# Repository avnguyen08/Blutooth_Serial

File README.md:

# Blutooth Serial

Board that steps down 24V to 3.3V and uses a HC-05 for UART to blutooth classic data conversion

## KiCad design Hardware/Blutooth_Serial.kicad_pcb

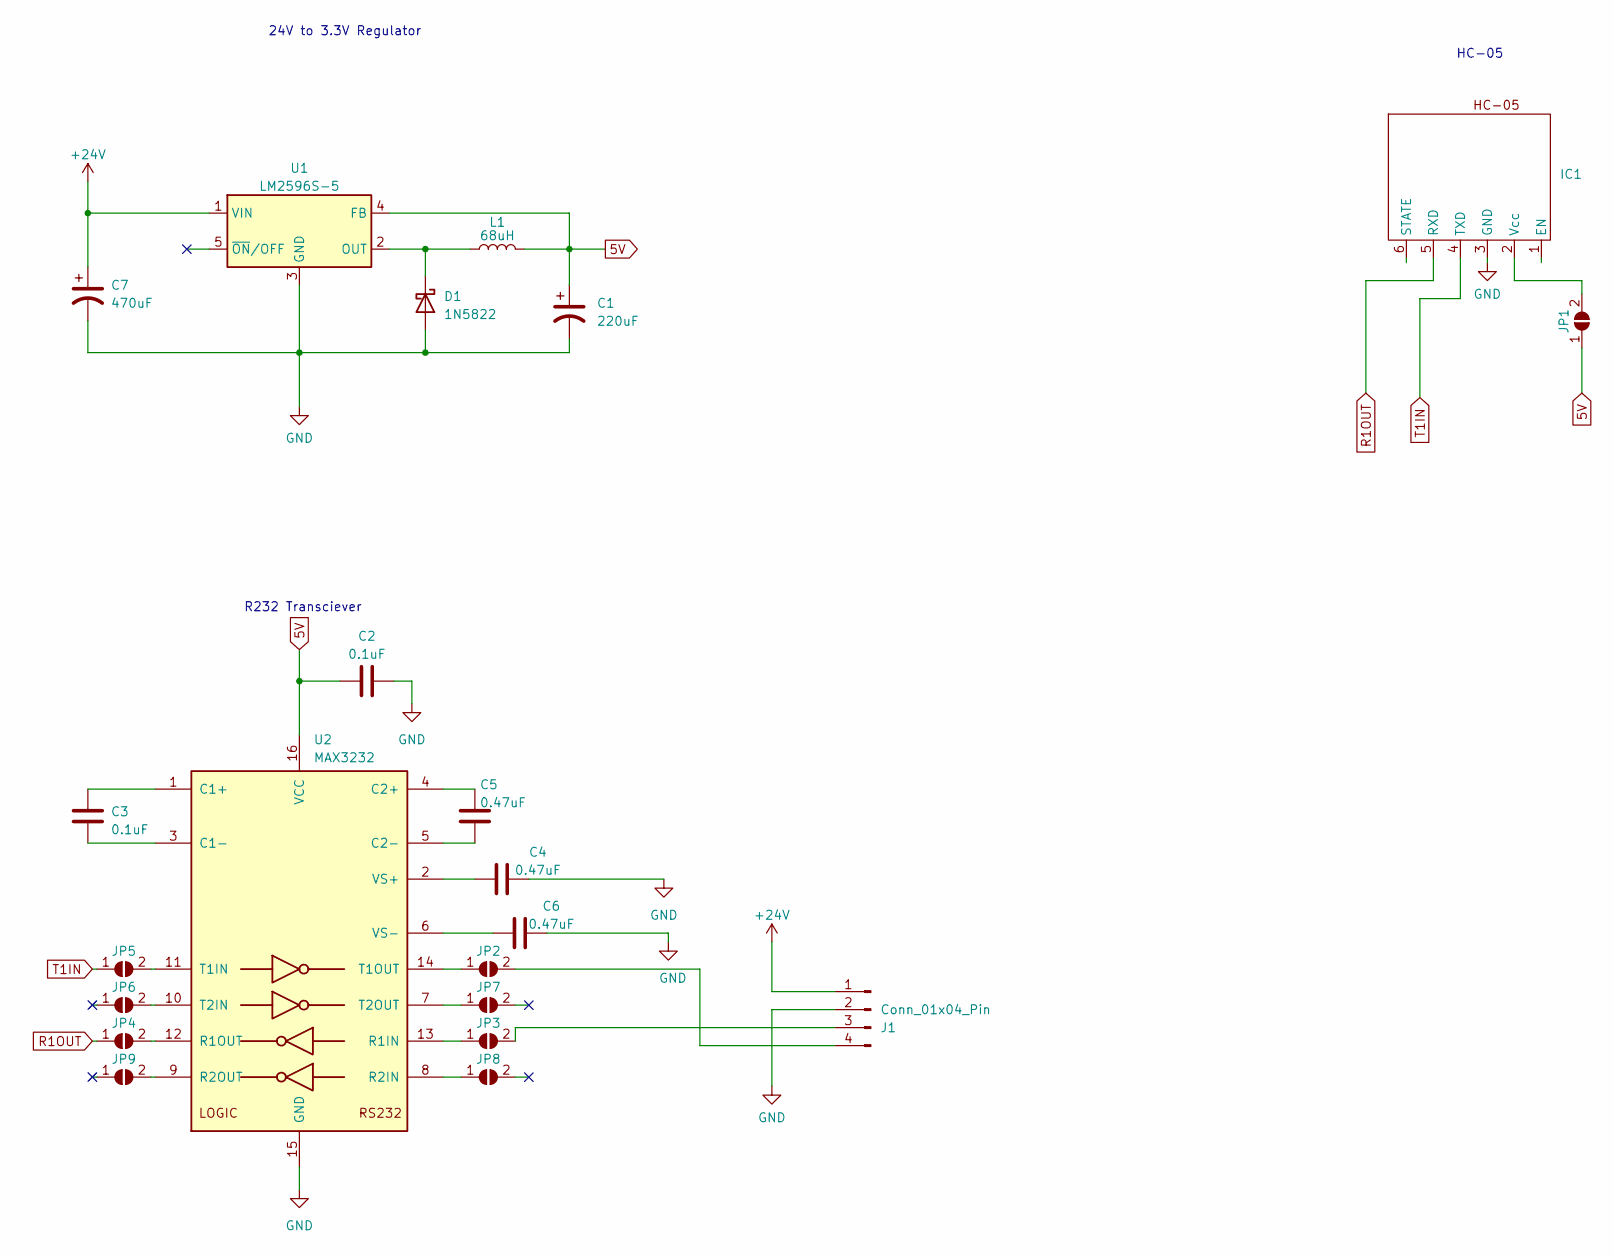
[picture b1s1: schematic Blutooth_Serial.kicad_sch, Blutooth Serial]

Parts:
C1: 220uF; 220uF_SMD_CAP
C2, C3: 0.1uF; C_0805_2012Metric
C4, C5, C6: 0.47uF; C_0805_2012Metric
C7: 470uF; 470uF_SMD_CAP
D1: 1N5822; D_0805_2012Metric
IC1: HC-05
J1: Conn_01x04_Pin; male_pin_4
JP1, JP2, JP3, JP4, JP5, JP6, JP7, JP8, JP9: SolderJumper_2_Open; SolderJumper-2_P1.3mm_Open_Pad1.0x1.5mm
L1: 68uH; L_12x12mm_H6mm
U1: LM2596S-5; TO-263-5_TabPin3
U2: MAX3232; MAX3232EIDR

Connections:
5V: C1.1, C2.1, JP1.1 (A), L1.2, U1.4 (FB), U2.16 (VCC)
+24V: C7.1, J1.1, U1.1 (VIN)
GND: C1.2, C2.2, C4.2, C6.2, C7.2, D1.2 (A), IC1.3 (GND), J1.2, U1.3 (GND), U2.15 (GND)
unnamed: D1.1 (K), L1.1, U1.2 (OUT)
unnamed: IC1.2 (Vcc), JP1.2 (B)
unnamed: J1.3, JP3.2 (B)
unnamed: J1.4, JP2.2 (B)
unnamed: JP2.1 (A), U2.14 (T1OUT)
unnamed: JP3.1 (A), U2.13 (R1IN)
unnamed: JP4.2 (B), U2.12 (R1OUT)
unnamed: JP5.2 (B), U2.11 (T1IN)
unnamed: JP6.2 (B), U2.10 (T2IN)
unnamed: JP7.1 (A), U2.7 (T2OUT)
unnamed: JP8.1 (A), U2.8 (R2IN)
unnamed: JP9.2 (B), U2.9 (R2OUT)
unnamed: C3.1, U2.1 (C1+)
unnamed: C3.2, U2.3 (C1-)
unnamed: C5.1, U2.4 (C2+)
unnamed: C5.2, U2.5 (C2-)
unnamed: C4.1, U2.2 (VS+)
unnamed: C6.1, U2.6 (VS-)
R1OUT: IC1.5 (RXD), JP4.1 (A)
T1IN: IC1.4 (TXD), JP5.1 (A)

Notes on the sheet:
R232 Transciever
24V to 3.3V Regulator
HC-05

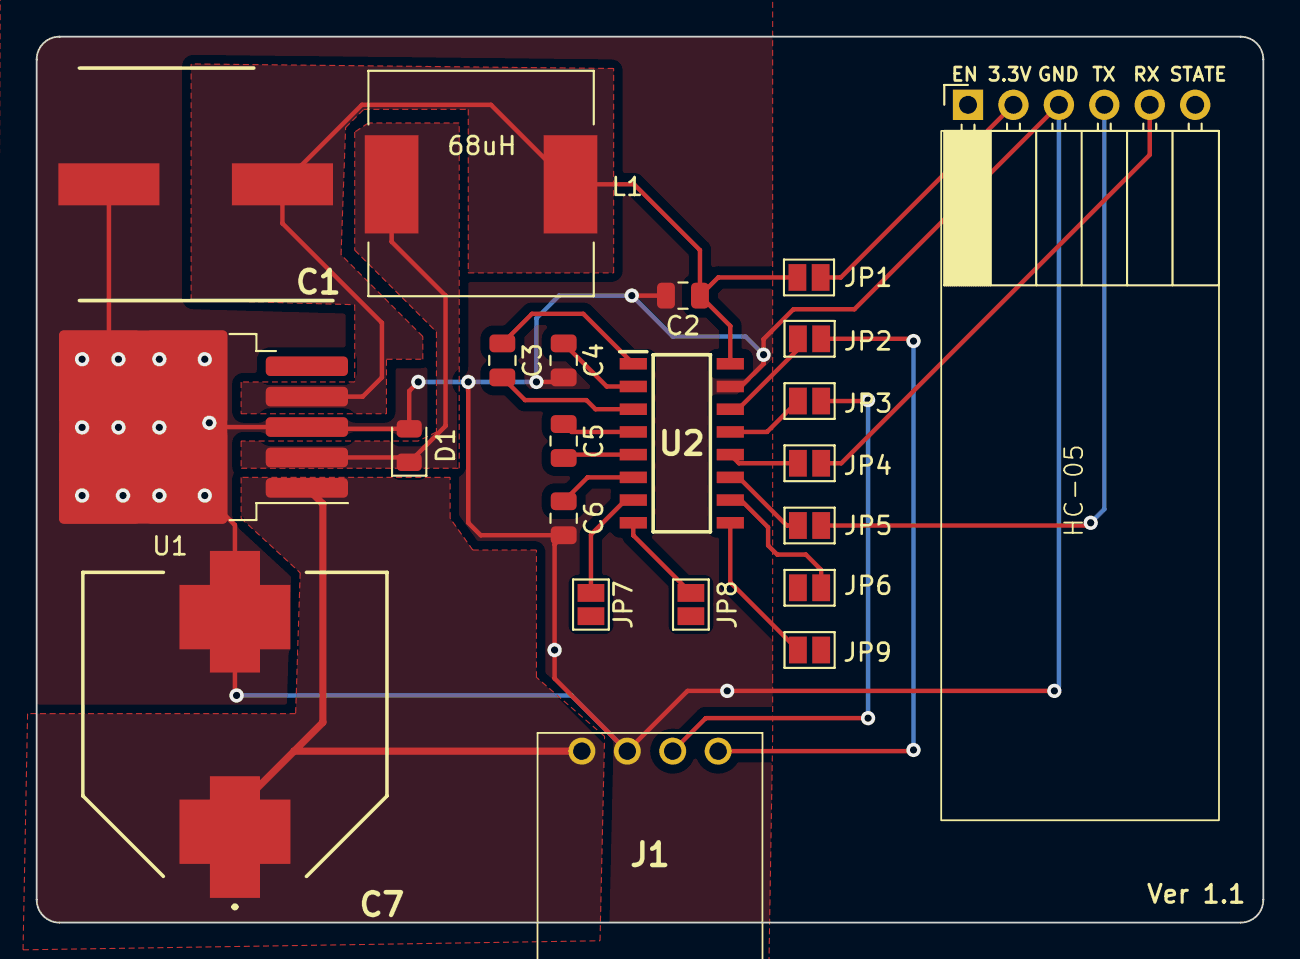
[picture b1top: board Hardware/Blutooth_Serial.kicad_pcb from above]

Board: 2 copper layers, 68.6 x 49.5 mm, 22 parts (0 on the bottom side), 23 nets.

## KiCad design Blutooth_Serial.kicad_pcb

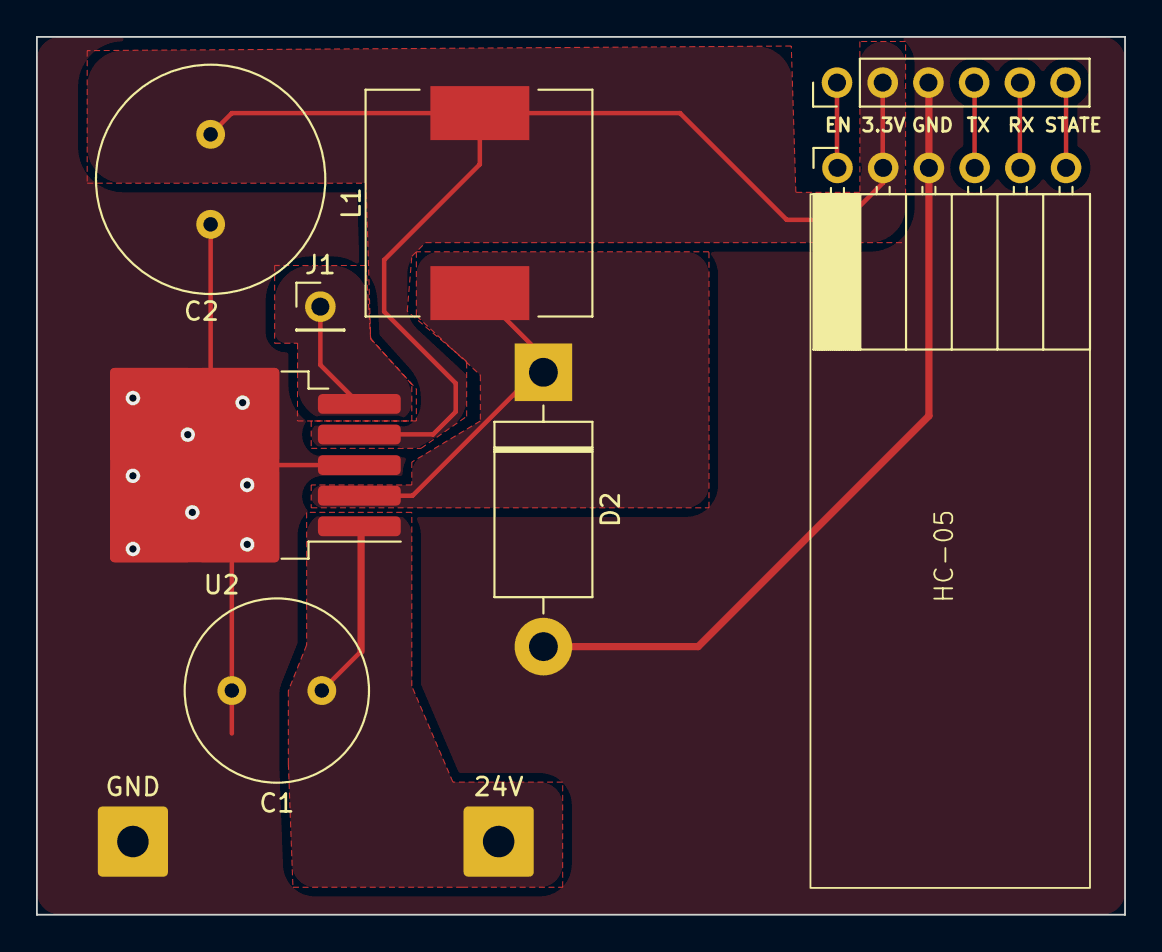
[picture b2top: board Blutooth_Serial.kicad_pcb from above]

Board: 2 copper layers, 60.5 x 48.8 mm, 9 parts (0 on the bottom side), 5 nets.

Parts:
C1: 150uF; C_Radial_D10.0mm_H16.0mm_P5.00mm
C2: 680uF; C_Radial_D12.5mm_H25.0mm_P5.00mm
D2: 1N5822; D_DO-201AD_P15.24mm_Horizontal
GND: SolderWire-1sqmm_1x01_D1.4mm_OD3.9mm
IC1: HC-05
J1: Test_Pad; PinHeader_1x01_P2.54mm_Vertical
L1: 33uH; L_12x12mm_H6mm
U2: LM2596S-3.3; TO-263-5_TabPin3
VIN+: (no value)

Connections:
3.3V: C2.1, IC1.2 (Vcc), L1.2, U2.4 (FB)
+24V: C1.1, U2.1 (VIN), VIN+.1
GND: C1.2, C2.2, D2.2 (A), GND.1, IC1.3 (GND), U2.3 (GND)
unnamed: D2.1 (K), L1.1, U2.2 (OUT)
unnamed: J1.1, U2.5 (~ON/OFF)

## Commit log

2023-12-28 First board order
2024-01-15 Added Software tests
2024-01-26 code changes
2024-01-30 updated schematic
2024-01-31 reorganized and switched components
2024-03-15 small edits
